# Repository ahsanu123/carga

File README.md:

# 💈 Carga

Carga project is intended to create automatic weighing machine with feeder and auto dispenser, will trying to create firmware with rust 🦀.

### 🌳 Project Log

- 24 Februari 2025 - Initial Project Commit
- 24 Maret 2026 - Reseting Project structure and create roadmap

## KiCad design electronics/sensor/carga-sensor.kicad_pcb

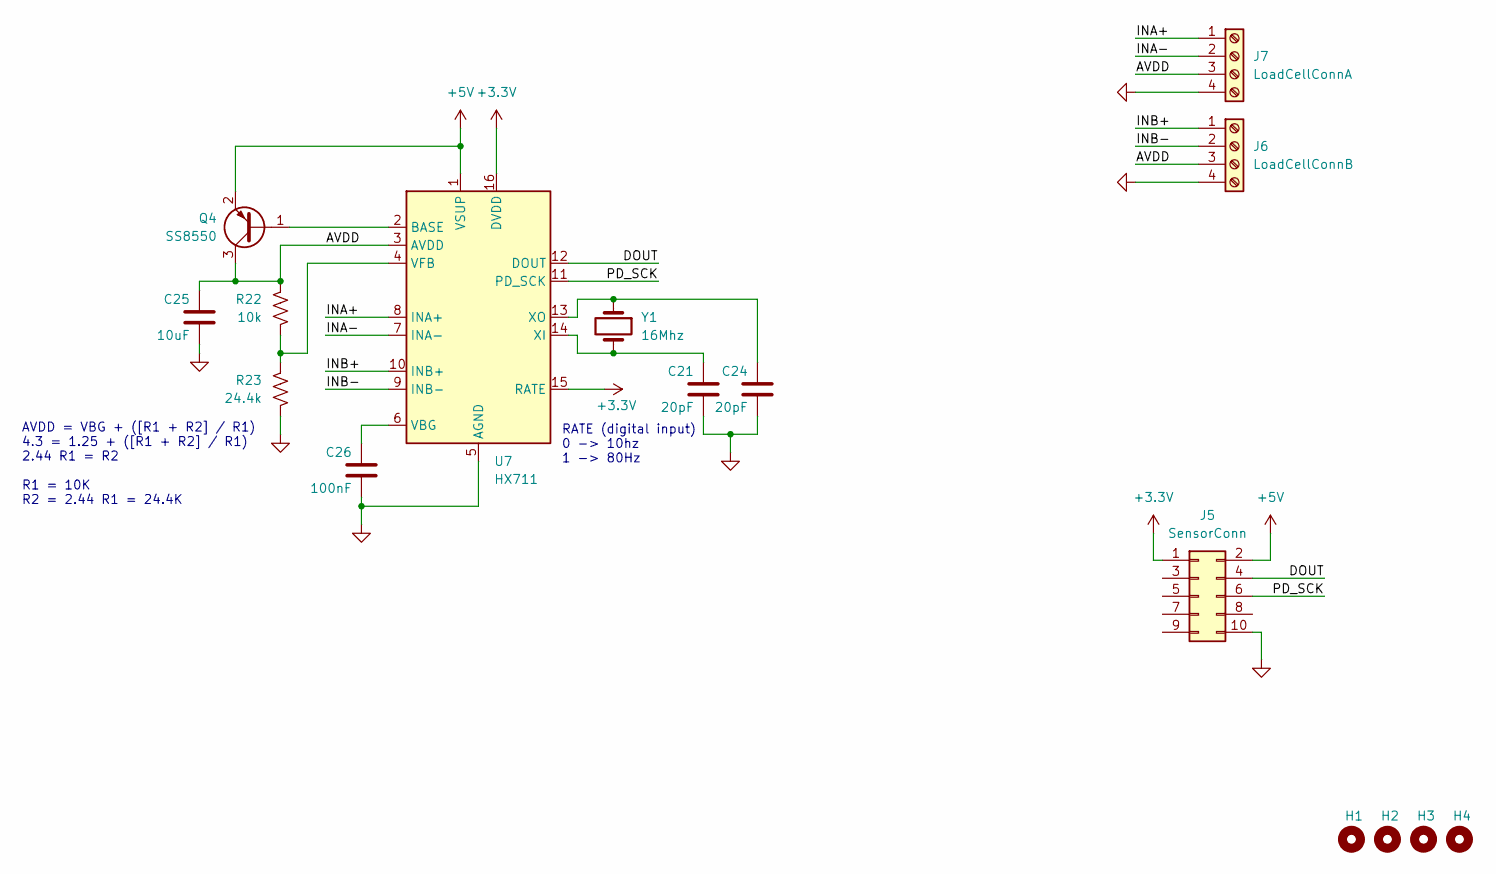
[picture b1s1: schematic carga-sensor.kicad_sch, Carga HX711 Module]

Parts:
C21, C24: 20pF; C_0805_2012Metric_Pad1.18x1.45mm_HandSolder
C25: 10uF; C_0805_2012Metric_Pad1.18x1.45mm_HandSolder
C26: 100nF; C_0805_2012Metric_Pad1.18x1.45mm_HandSolder
H1, H2, H3, H4: MountingHole; MountingHole_2mm
J5: SensorConn; IDC-Header_2x05_P2.54mm_Vertical
J6: LoadCellConnB; TerminalBlock_Phoenix_PT-1,5-4-5.0-H_1x04_P5.00mm_Horizontal
J7: LoadCellConnA; TerminalBlock_Phoenix_PT-1,5-4-5.0-H_1x04_P5.00mm_Horizontal
Q4: SS8550; SOT-23
R22: 10k; R_0805_2012Metric_Pad1.20x1.40mm_HandSolder
R23: 24.4k; R_0805_2012Metric_Pad1.20x1.40mm_HandSolder
U7: HX711; SOIC-16_3.9x9.9mm_P1.27mm
Y1: 16Mhz; Crystal_HC49-U_Vertical

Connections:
+3.3V: J5.1, U7.15 (RATE), U7.16 (DVDD)
+5V: J5.2, Q4.2 (E), U7.1 (VSUP)
/AVDD: C25.1, J6.3, J7.3, Q4.3 (C), R22.1, U7.3 (AVDD)
/DOUT: J5.4, U7.12 (DOUT)
/INA+: J7.1, U7.8 (INA+)
/INA-: J7.2, U7.7 (INA-)
/INB+: J6.1, U7.10 (INB+)
/INB-: J6.2, U7.9 (INB-)
/PD_SCK: J5.6, U7.11 (PD_SCK)
GND: C21.2, C24.2, C25.2, C26.2, J5.10, J6.4, J7.4, R23.2, U7.5 (AGND)
unnamed: Q4.1 (B), U7.2 (BASE)
unnamed: C26.1, U7.6 (VBG)
unnamed: R22.2, R23.1, U7.4 (VFB)
unnamed: C21.1, U7.14 (XI), Y1.2
unnamed: C24.1, U7.13 (XO), Y1.1

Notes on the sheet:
AVDD = VBG + ([R1 + R2] / R1) 4.3 = 1.25 + ([R1 + R2] / R1) 2.44 R1 = R2 R1 = 10K R2 = 2.44 R1 = 24.4K
RATE (digital input) 0 -> 10hz 1 -> 80Hz

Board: 2 copper layers, 16 parts (0 on the bottom side), 15 nets, no tracks yet.

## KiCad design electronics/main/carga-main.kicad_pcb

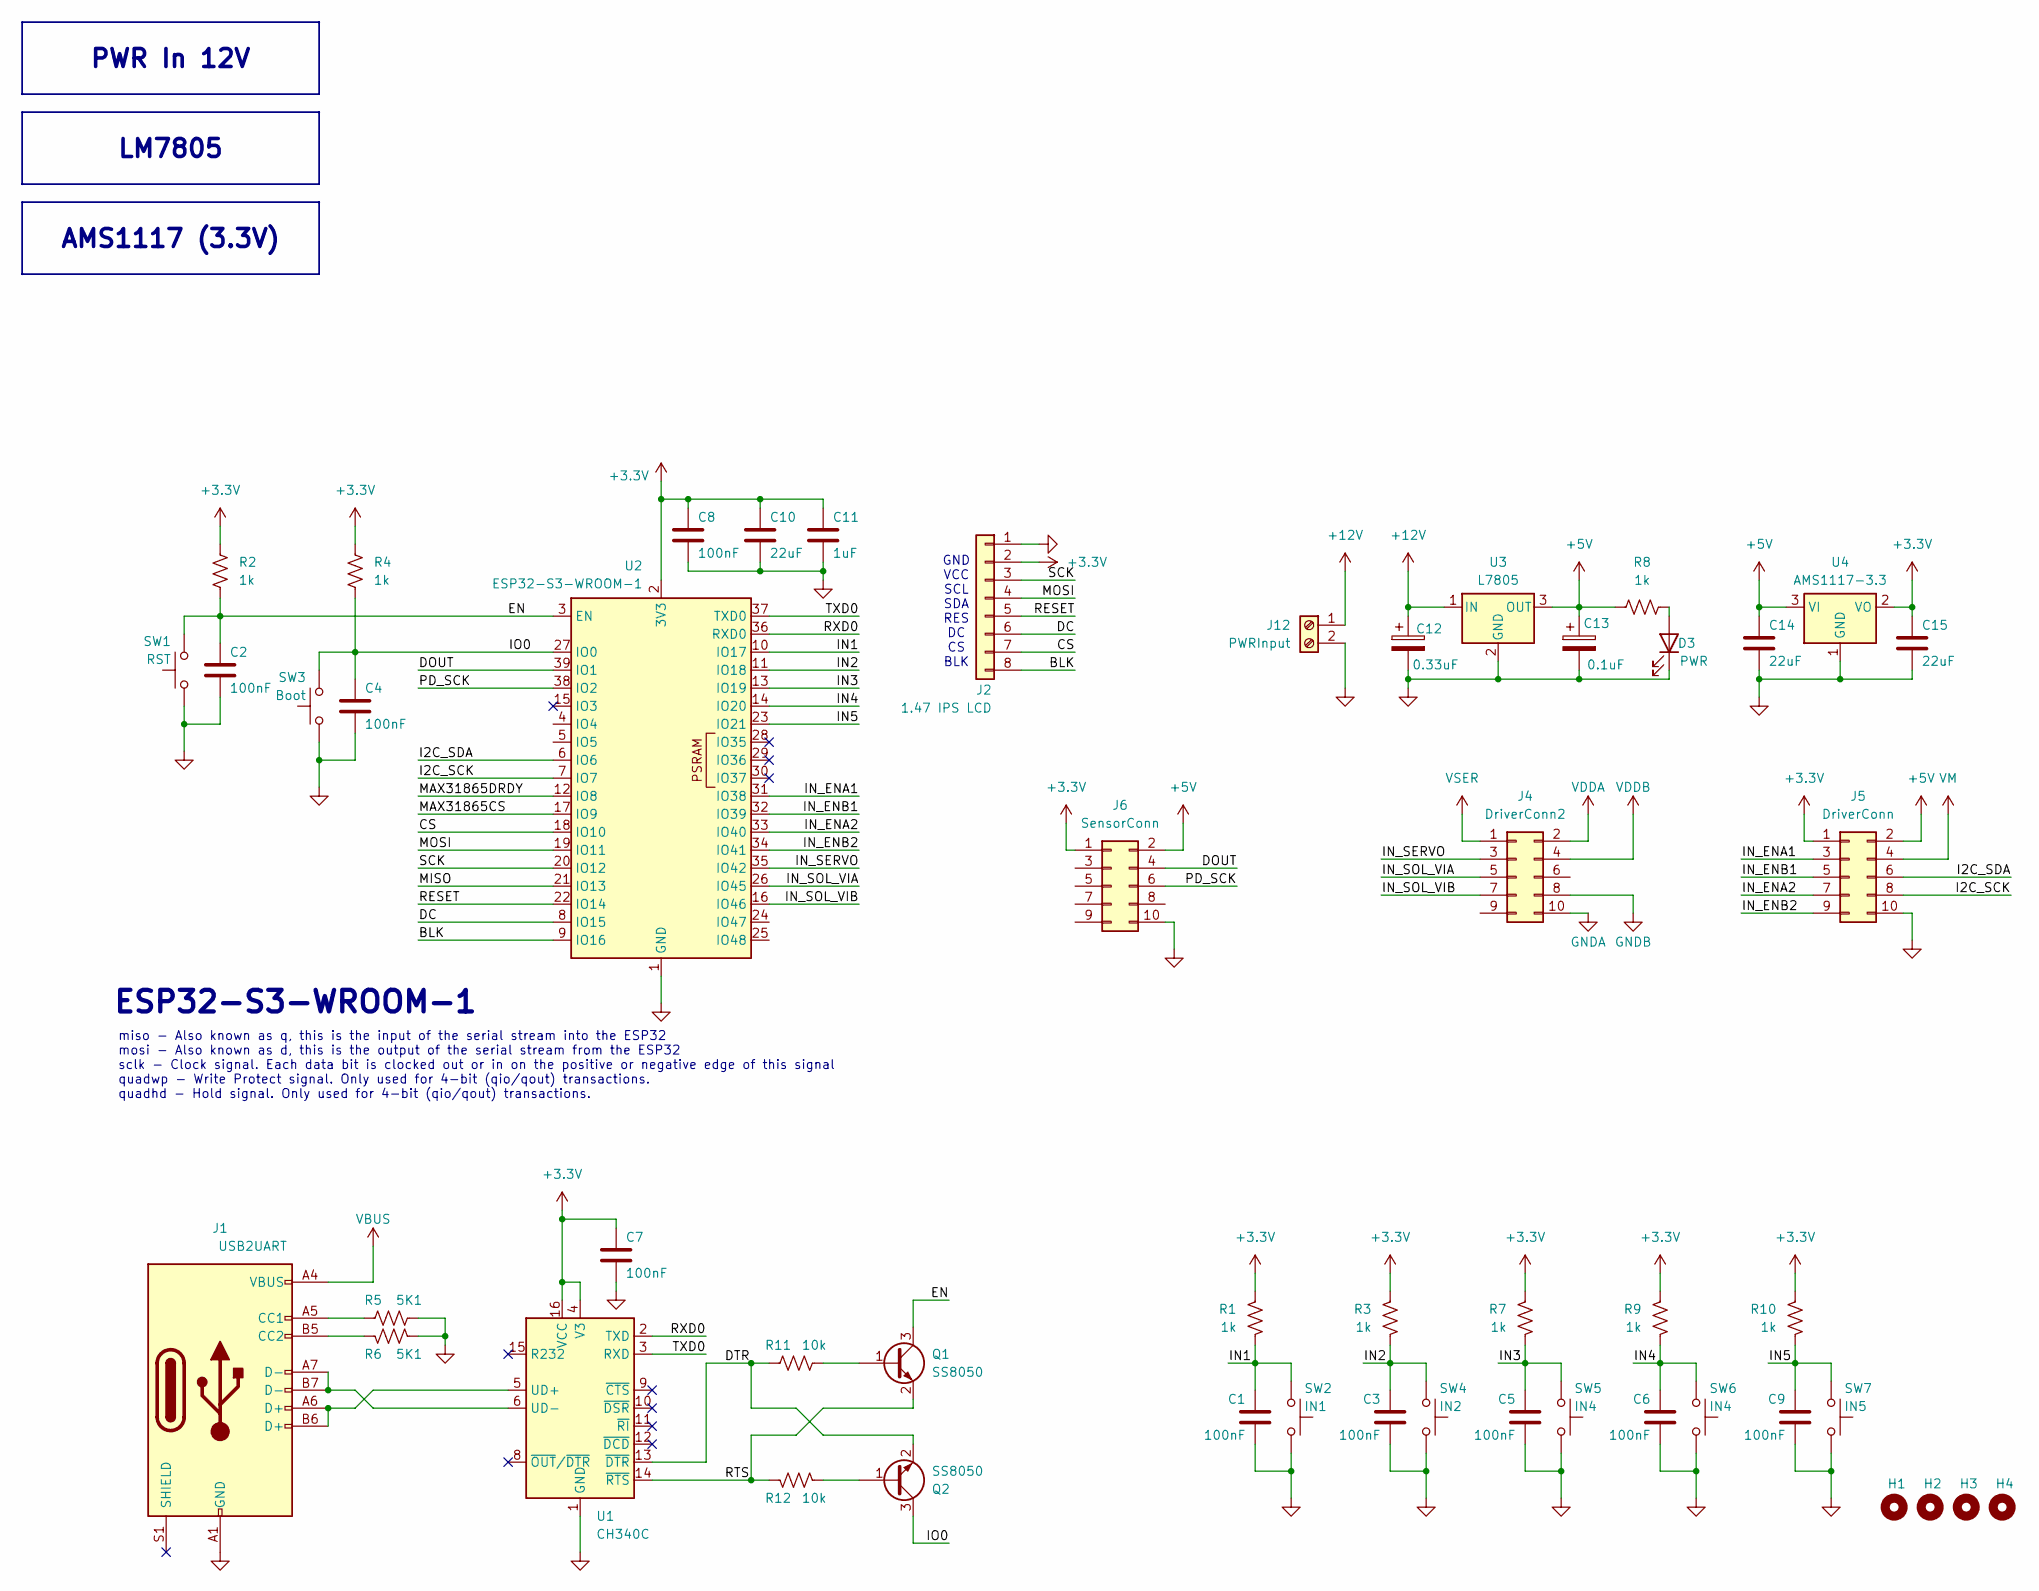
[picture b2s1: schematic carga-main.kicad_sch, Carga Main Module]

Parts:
C1, C2, C3, C4, C5, C6, C7, C8, C9: 100nF; C_0805_2012Metric_Pad1.18x1.45mm_HandSolder
C10, C14, C15: 22uF; C_0805_2012Metric_Pad1.18x1.45mm_HandSolder
C11: 1uF; C_0805_2012Metric_Pad1.18x1.45mm_HandSolder
C12: 0.33uF; C_0805_2012Metric_Pad1.18x1.45mm_HandSolder
C13: 0.1uF; C_0805_2012Metric_Pad1.18x1.45mm_HandSolder
D3: PWR; LED_1206_3216Metric_Pad1.42x1.75mm_HandSolder
H1, H2, H3, H4: MountingHole; MountingHole_2mm
J1: USB2UART; USB_C_Receptacle_GCT_USB4110
J2: 1.47 IPS LCD; PinHeader_1x08_P2.54mm_Vertical
J4: DriverConn2; IDC-Header_2x05_P2.54mm_Vertical
J5: DriverConn; IDC-Header_2x05_P2.54mm_Vertical
J6: SensorConn; IDC-Header_2x05_P2.54mm_Vertical
J12: PWRInput; TerminalBlock_Phoenix_PT-1,5-2-5.0-H_1x02_P5.00mm_Horizontal
Q1, Q2: SS8050; SOT-23_Handsoldering
R1, R2, R3, R4, R7, R8, R9, R10: 1k; R_0805_2012Metric_Pad1.20x1.40mm_HandSolder
R5, R6: 5K1; R_0805_2012Metric_Pad1.20x1.40mm_HandSolder
R11, R12: 10k; R_0805_2012Metric_Pad1.20x1.40mm_HandSolder
SW1: RST; SW_SPST_PTS810
SW2: IN1; SW_SPST_Omron_B3FS-100xP
SW3: Boot; SW_SPST_PTS810
SW4: IN2; SW_SPST_Omron_B3FS-100xP
SW5, SW6: IN4; SW_SPST_Omron_B3FS-100xP
SW7: IN5; SW_SPST_Omron_B3FS-100xP
U1: CH340C; SOIC-16_3.9x9.9mm_P1.27mm
U2: ESP32-S3-WROOM-1
U3: L7805; TO-220F-3_Horizontal_TabDown
U4: AMS1117-3.3; SOT-223-3_TabPin2

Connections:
+3.3V: C7.1, C8.1, C10.1, C11.1, C15.1, J2.2, J5.1, J6.1, R1.1, R2.1, R3.1, R4.1, R7.1, R9.1, R10.1, U1.4 (V3), U1.16 (VCC), U2.2 (3V3), U4.2 (VO)
+5V: C13.1, C14.1, J5.2, J6.2, R8.1, U3.3 (OUT), U4.3 (VI)
+12V: C12.1, J12.1, U3.1 (IN)
/BLK: J2.8, U2.9 (IO16)
/CS: J2.7, U2.18 (IO10)
/DC: J2.6, U2.8 (IO15)
/DOUT: J6.4, U2.39 (IO1)
/DTR: Q2.2 (E), R11.2, U1.13 (~DTR)
/EN: C2.1, Q1.3 (C), R2.2, SW1.2, U2.3 (EN)
/I2C_SCK: J5.8, U2.7 (IO7)
/I2C_SDA: J5.6, U2.6 (IO6)
/IN1: C1.1, R1.2, SW2.2, U2.10 (IO17)
/IN2: C3.1, R3.2, SW4.2, U2.11 (IO18)
/IN3: C5.1, R7.2, SW5.2, U2.13 (IO19)
/IN4: C6.1, R9.2, SW6.2, U2.14 (IO20)
/IN5: C9.1, R10.2, SW7.2, U2.23 (IO21)
/IN_ENA1: J5.3, U2.31 (IO38)
/IN_ENA2: J5.7, U2.33 (IO40)
/IN_ENB1: J5.5, U2.32 (IO39)
/IN_ENB2: J5.9, U2.34 (IO41)
/IN_SERVO: J4.3, U2.35 (IO42)
/IN_SOL_VIA: J4.5, U2.26 (IO45)
/IN_SOL_VIB: J4.7, U2.16 (IO46)
/IO0: C4.1, Q2.3 (C), R4.2, SW3.2, U2.27 (IO0)
/MAX31865CS: U2.17 (IO9)
/MAX31865DRDY: U2.12 (IO8)
/MISO: U2.21 (IO13)
/MOSI: J2.4, U2.19 (IO11)
/PD_SCK: J6.6, U2.38 (IO2)
/RESET: J2.5, U2.22 (IO14)
/RTS: Q1.2 (E), R12.2, U1.14 (~RTS)
/RXD0: U1.2 (TXD), U2.36 (RXD0)
/SCK: J2.3, U2.20 (IO12)
/TXD0: U1.3 (RXD), U2.37 (TXD0)
GND: C1.2, C2.2, C3.2, C4.2, C5.2, C6.2, C7.2, C8.2, C9.2, C10.2, C11.2, C12.2, C13.2, C14.2, C15.2, D3.1 (K), J1.A1 (GND), J1.A12 (GND), J1.B1 (GND), J1.B12 (GND), J2.1, J5.10, J6.10, J12.2, R5.1, R6.1, SW1.1, SW2.1, SW3.1, SW4.1, SW5.1, SW6.1, SW7.1, U1.1 (GND), U2.1 (GND), U2.40 (GND), U2.41 (GND), U3.2 (GND), U4.1 (GND)
GNDA: J4.10
GNDB: J4.8
unnamed: D3.2 (A), R8.2
unnamed: J1.A5 (CC1), R5.2
unnamed: J1.B5 (CC2), R6.2
unnamed: Q1.1 (B), R11.1
unnamed: Q2.1 (B), R12.1
unnamed: J1.A6 (D+), J1.B6 (D+), U1.5 (UD+)
unnamed: J1.A7 (D-), J1.B7 (D-), U1.6 (UD-)
VBUS: J1.A4 (VBUS), J1.A9 (VBUS), J1.B4 (VBUS), J1.B9 (VBUS)
VDDA: J4.2
VDDB: J4.4
VM: J5.4
VSER: J4.1

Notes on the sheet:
miso - Also known as q, this is the input of the serial stream into the ESP32 mosi - Also known as d, this is the output of the serial stream from the ESP32 sclk - Clock signal. Each data bit is clocked out or in on the positive or negative edge of this signal quadwp - Write Protect signal. Only us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
ESP32-S3-WROOM-1
GND VCC SCL SDA RES DC CS BLK
LM7805
PWR In 12V
AMS1117 (3.3V)

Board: 2 copper layers, 51 parts (21 on the bottom side), 40 nets, no tracks yet.

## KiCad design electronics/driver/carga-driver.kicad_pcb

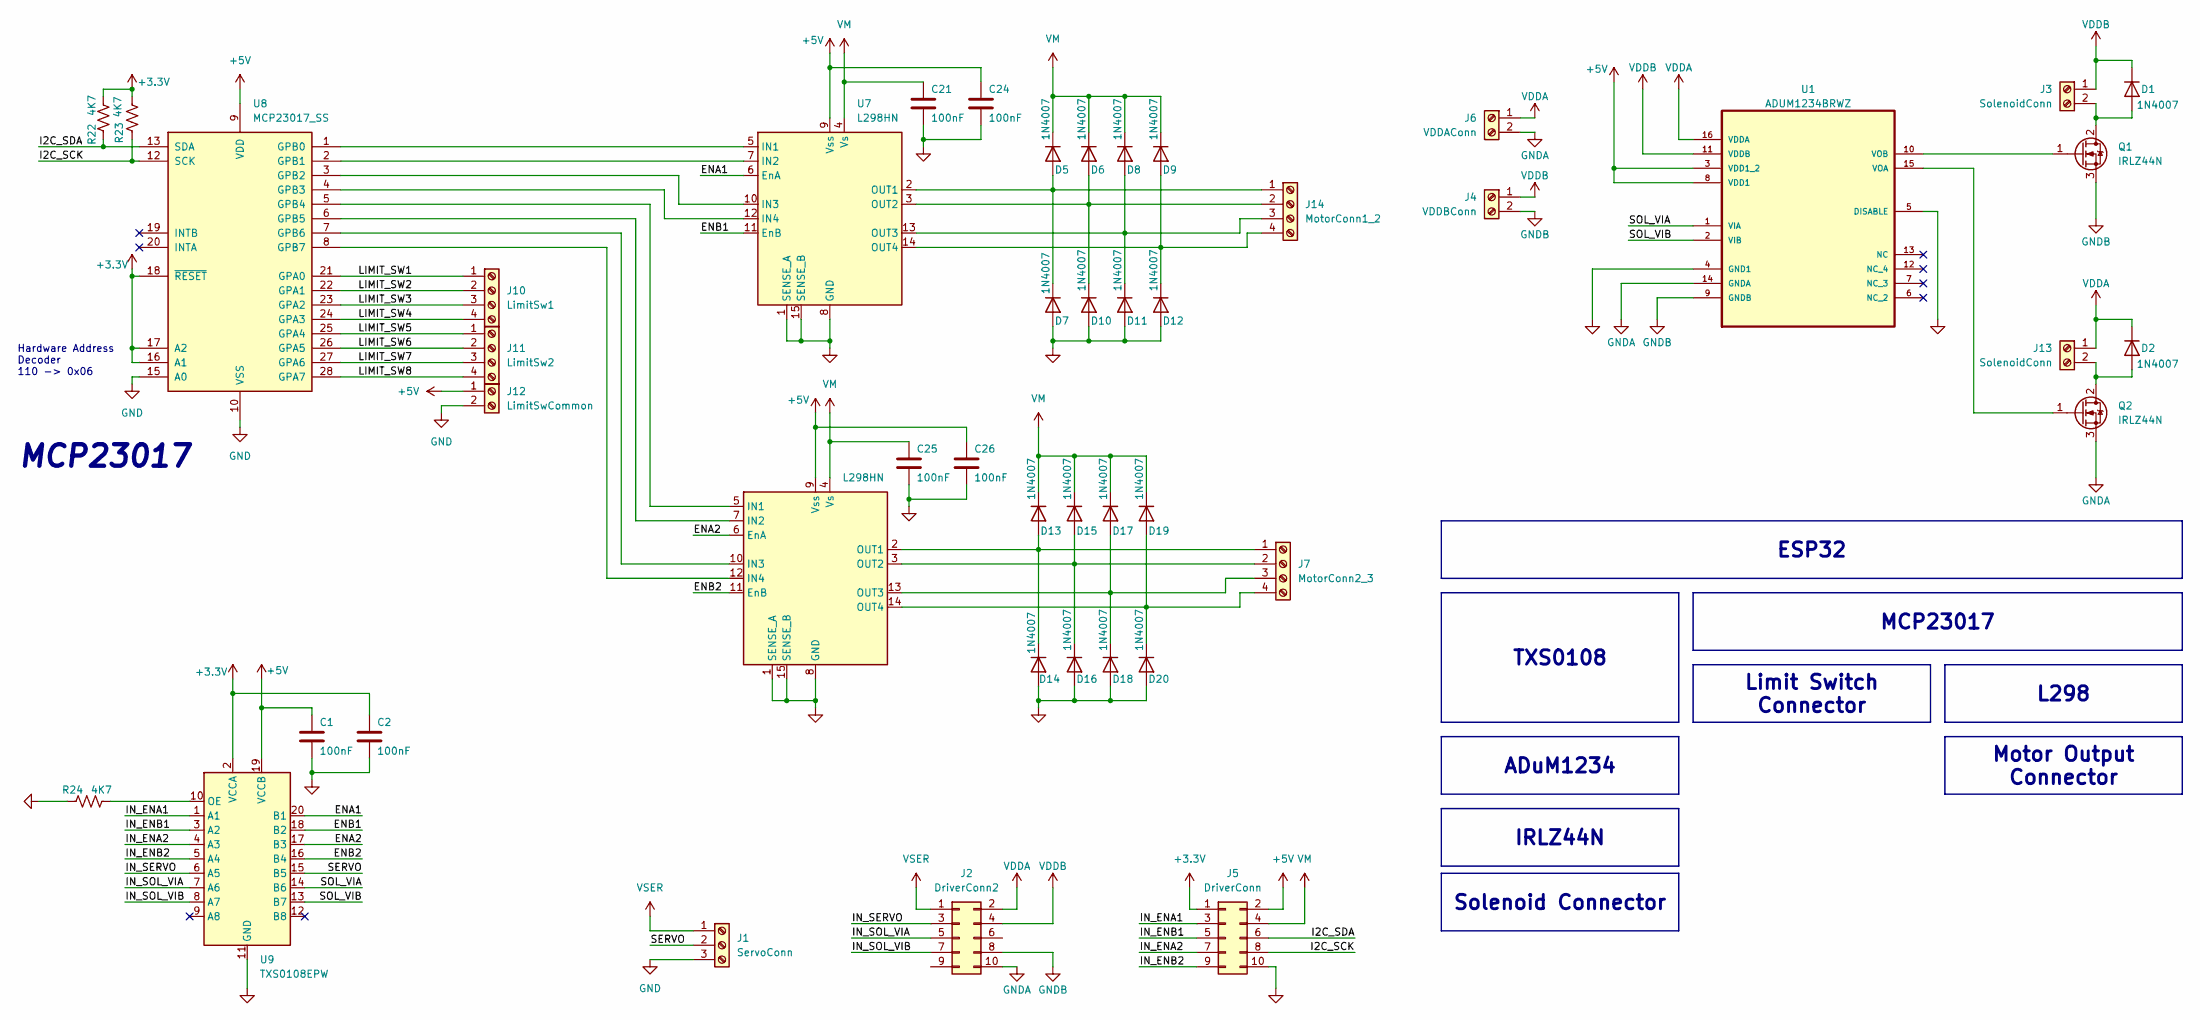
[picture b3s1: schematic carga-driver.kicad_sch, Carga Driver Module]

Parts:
C1, C2, C21, C24, C25, C26: 100nF; C_0805_2012Metric_Pad1.18x1.45mm_HandSolder
D1, D2, D5, D6, D7, D8, D9, D10, D11, D12, D13, D14, D15, D16, D17, D18, D19, D20: 1N4007; D_DO-41_SOD81_P10.16mm_Horizontal
J1: ServoConn; TerminalBlock_Phoenix_PT-1,5-3-5.0-H_1x03_P5.00mm_Horizontal
J2: DriverConn2; IDC-Header_2x05_P2.54mm_Vertical
J3, J13: SolenoidConn; TerminalBlock_Phoenix_PT-1,5-2-5.0-H_1x02_P5.00mm_Horizontal
J4: VDDBConn; TerminalBlock_Phoenix_PT-1,5-2-5.0-H_1x02_P5.00mm_Horizontal
J5: DriverConn; IDC-Header_2x05_P2.54mm_Vertical
J6: VDDAConn; TerminalBlock_Phoenix_PT-1,5-2-5.0-H_1x02_P5.00mm_Horizontal
J7: MotorConn2_3; TerminalBlock_Phoenix_PT-1,5-4-5.0-H_1x04_P5.00mm_Horizontal
J10: LimitSw1; TerminalBlock_Phoenix_PT-1,5-4-5.0-H_1x04_P5.00mm_Horizontal
J11: LimitSw2; TerminalBlock_Phoenix_PT-1,5-4-5.0-H_1x04_P5.00mm_Horizontal
J12: LimitSwCommon; TerminalBlock_Phoenix_PT-1,5-2-5.0-H_1x02_P5.00mm_Horizontal
J14: MotorConn1_2; TerminalBlock_Phoenix_PT-1,5-4-5.0-H_1x04_P5.00mm_Horizontal
Q1, Q2: IRLZ44N; TO-220-3_Horizontal_TabDown
R22, R23, R24: 4K7; R_0805_2012Metric_Pad1.20x1.40mm_HandSolder
U1: ADUM1234BRWZ; SOIC-16W_7.5x10.3mm_P1.27mm; MPN ADUM1234BRWZ
U7, U10: L298HN; TO-220-15_P2.54x2.54mm_StaggerOdd_Lead5.84mm_TabDown
U8: MCP23017_SS; SSOP-28_5.3x10.2mm_P0.65mm
U9: TXS0108EPW; TSSOP-20_4.4x6.5mm_P0.65mm

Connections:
+3.3V: C2.1, J5.1, R22.1, R23.1, U8.16 (A1), U8.17 (A2), U8.18 (~RESET), U9.2 (VCCA)
+5V: C1.1, C24.1, C26.1, J5.2, J12.1, U1.3 (VDD1_2), U1.8 (VDD1), U7.9 (Vss), U8.9 (VDD), U9.19 (VCCB), U10.9 (Vss)
/ENA1: U7.6 (EnA), U9.20 (B1)
/ENA2: U9.17 (B3), U10.6 (EnA)
/ENB1: U7.11 (EnB), U9.18 (B2)
/ENB2: U9.16 (B4), U10.11 (EnB)
/I2C_SCK: J5.8, R23.2, U8.12 (SCK)
/I2C_SDA: J5.6, R22.2, U8.13 (SDA)
/IN_ENA1: J5.3, U9.1 (A1)
/IN_ENA2: J5.7, U9.4 (A3)
/IN_ENB1: J5.5, U9.3 (A2)
/IN_ENB2: J5.9, U9.5 (A4)
/IN_SERVO: J2.3, U9.6 (A5)
/IN_SOL_VIA: J2.5, U9.7 (A6)
/IN_SOL_VIB: J2.7, U9.8 (A7)
/LIMIT_SW1: J10.1, U8.21 (GPA0)
/LIMIT_SW2: J10.2, U8.22 (GPA1)
/LIMIT_SW3: J10.3, U8.23 (GPA2)
/LIMIT_SW4: J10.4, U8.24 (GPA3)
/LIMIT_SW5: J11.1, U8.25 (GPA4)
/LIMIT_SW6: J11.2, U8.26 (GPA5)
/LIMIT_SW7: J11.3, U8.27 (GPA6)
/LIMIT_SW8: J11.4, U8.28 (GPA7)
/SERVO: J1.2, U9.15 (B5)
/SOL_VIA: U1.1 (VIA), U9.14 (B6)
/SOL_VIB: U1.2 (VIB), U9.13 (B7)
GND: C1.2, C2.2, C21.2, C24.2, C25.2, C26.2, D7.2 (A), D10.2 (A), D11.2 (A), D12.2 (A), D14.2 (A), D16.2 (A), D18.2 (A), D20.2 (A), J1.3, J5.10, J12.2, R24.2, U1.4 (GND1), U1.5 (DISABLE), U7.1 (SENSE_A), U7.8 (GND), U7.15 (SENSE_B), U8.10 (VSS), U8.15 (A0), U9.11 (GND), U10.1 (SENSE_A), U10.8 (GND), U10.15 (SENSE_B)
GNDA: J2.10, J6.2, Q2.3 (S), U1.14 (GNDA)
GNDB: J2.8, J4.2, Q1.3 (S), U1.9 (GNDB)
unnamed: D1.2 (A), J3.2, Q1.2 (D)
unnamed: D2.2 (A), J13.2, Q2.2 (D)
unnamed: D5.2 (A), D7.1 (K), J14.1, U7.2 (OUT1)
unnamed: D6.2 (A), D10.1 (K), J14.2, U7.3 (OUT2)
unnamed: D8.2 (A), D11.1 (K), J14.3, U7.13 (OUT3)
unnamed: D9.2 (A), D12.1 (K), J14.4, U7.14 (OUT4)
unnamed: D13.2 (A), D14.1 (K), J7.1, U10.2 (OUT1)
unnamed: D15.2 (A), D16.1 (K), J7.2, U10.3 (OUT2)
unnamed: D17.2 (A), D18.1 (K), J7.3, U10.13 (OUT3)
unnamed: D19.2 (A), D20.1 (K), J7.4, U10.14 (OUT4)
unnamed: Q1.1 (G), U1.10 (VOB)
unnamed: Q2.1 (G), U1.15 (VOA)
unnamed: U7.5 (IN1), U8.1 (GPB0)
unnamed: U7.7 (IN2), U8.2 (GPB1)
unnamed: U7.10 (IN3), U8.3 (GPB2)
unnamed: U7.12 (IN4), U8.4 (GPB3)
unnamed: R24.1, U9.10 (OE)
unnamed: U8.5 (GPB4), U10.5 (IN1)
unnamed: U8.6 (GPB5), U10.7 (IN2)
unnamed: U8.7 (GPB6), U10.10 (IN3)
unnamed: U8.8 (GPB7), U10.12 (IN4)
VDDA: D2.1 (K), J2.2, J6.1, J13.1, U1.16 (VDDA)
VDDB: D1.1 (K), J2.4, J3.1, J4.1, U1.11 (VDDB)
VM: C21.1, C25.1, D5.1 (K), D6.1 (K), D8.1 (K), D9.1 (K), D13.1 (K), D15.1 (K), D17.1 (K), D19.1 (K), J5.4, U7.4 (Vs), U10.4 (Vs)
VSER: J1.1, J2.1

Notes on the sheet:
MCP23017
Hardware Address Decoder 110 -> 0x06
IRLZ44N
Solenoid Connector
ADuM1234
L298
MCP23017
Motor Output Connector
TXS0108
Limit Switch Connector
ESP32

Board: 2 copper layers, 46 parts (0 on the bottom side), 54 nets, no tracks yet.

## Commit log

2026-03-24 initial weigher commit
2026-03-24 feat: add electronics projects
2026-03-24 feat: add firmware v1 projects
2026-03-24 feat: add mechanical v1 projects
2026-03-25 feat: create hx711 module schematic
2026-03-26 feat: create l298, mcp23017 driver module
2026-03-27 feat: add ADuM1234 and IRLZ44N for driving Solenoid
2026-03-27 feat: generate carga driver pcb
2026-03-27 feat: generate carga sensor pcb
2026-03-27 feat: add voltage regulator to carga main
2026-03-30 chore: flip mosi miso pin
2026-03-31 feat: arrange component in carga main
2026-04-01 feat: ble bas bounding is compiled with latest esp-hal and trouble github patch
2026-04-01 feat: able to connect with android and able to see battery percentage
2026-04-17 chore: update to kicad 10
